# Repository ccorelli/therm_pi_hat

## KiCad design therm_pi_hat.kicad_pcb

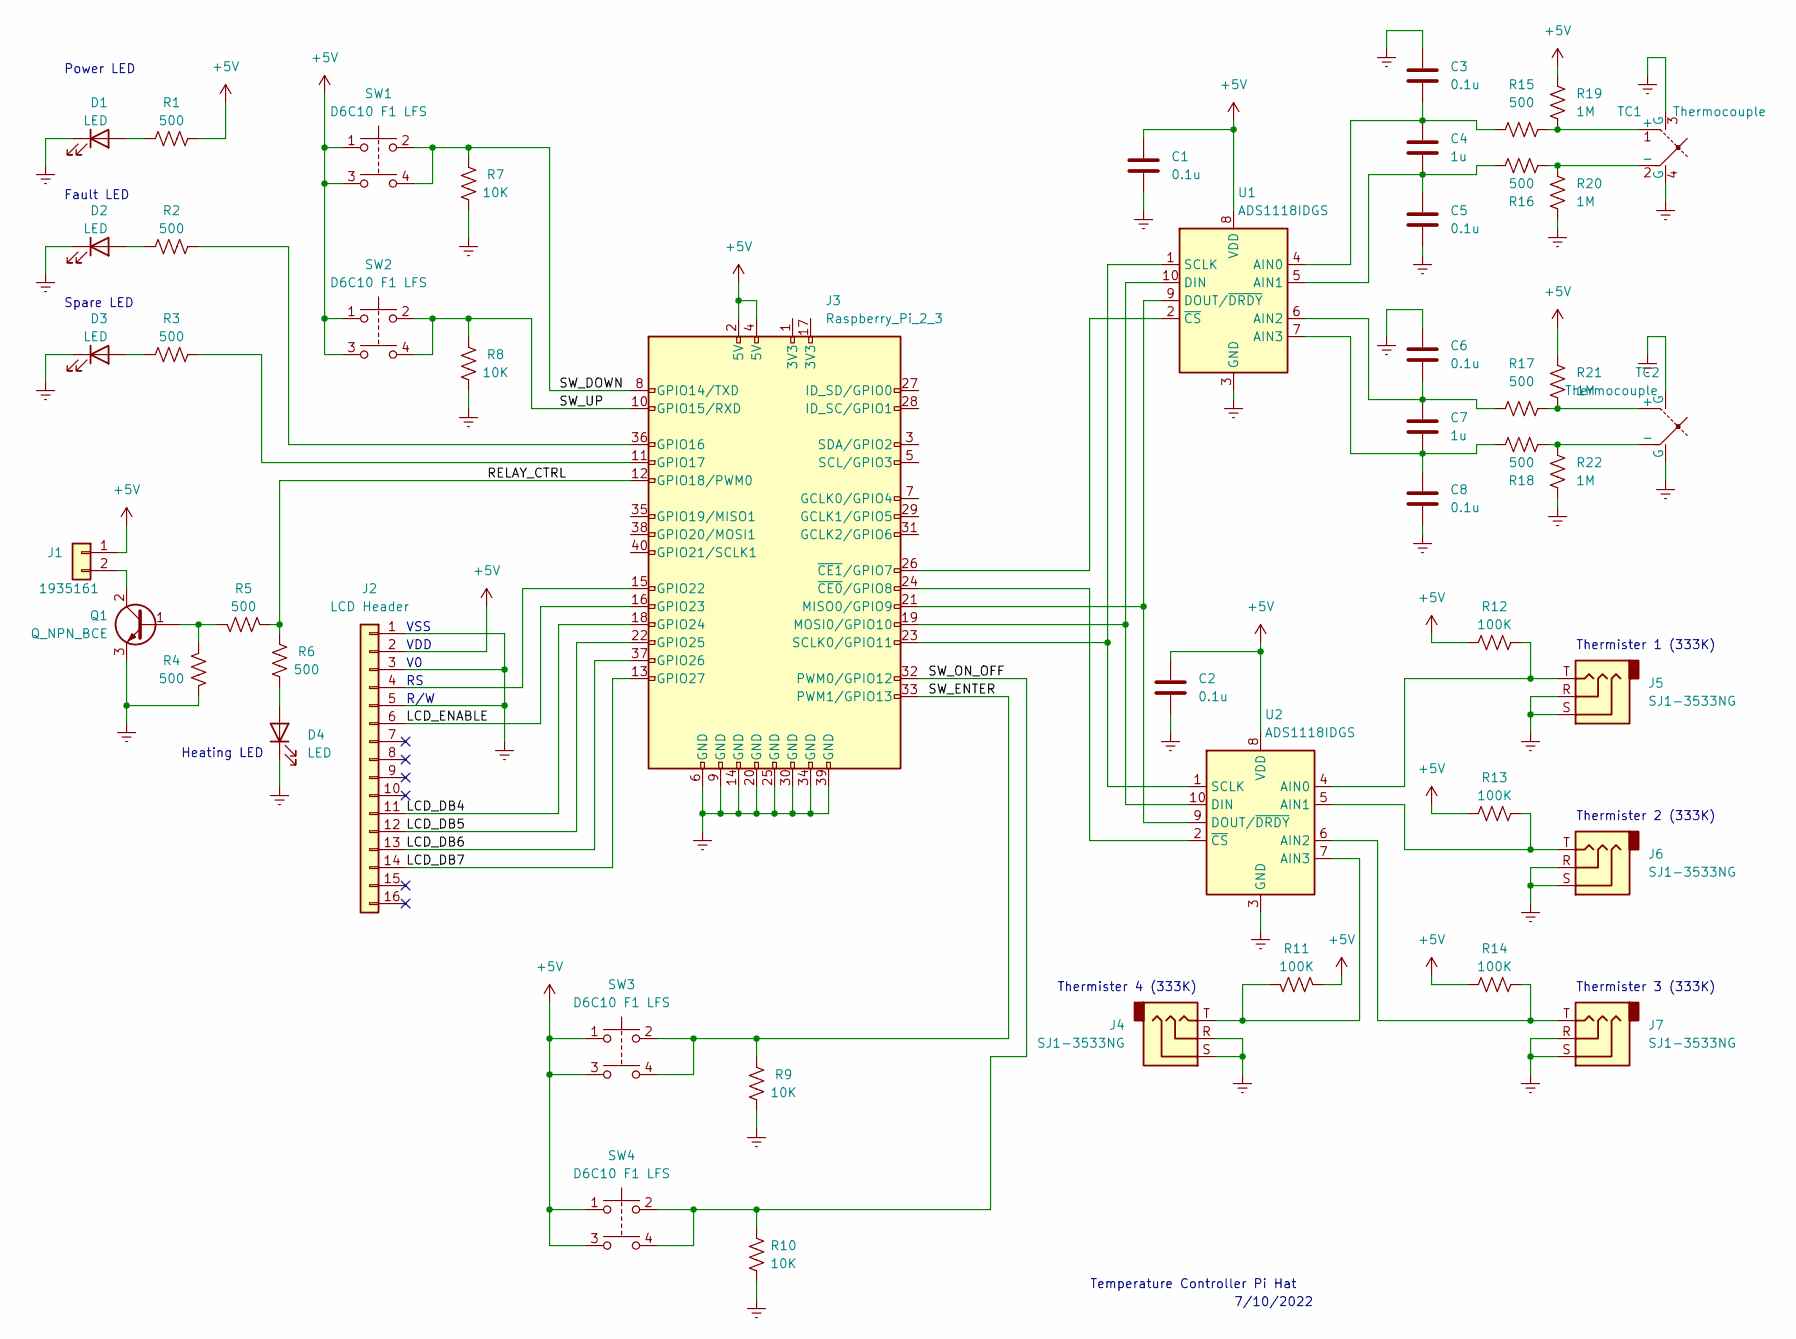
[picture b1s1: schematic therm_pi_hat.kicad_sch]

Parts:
C1, C2, C3, C5, C6, C8: 0.1u; C_Rect_L7.2mm_W3.5mm_P5.00mm_FKS2_FKP2_MKS2_MKP2
C4, C7: 1u; C_Rect_L7.2mm_W3.5mm_P5.00mm_FKS2_FKP2_MKS2_MKP2
D1, D2, D3, D4: LED; LED_D3.0mm_FlatTop
J1: 1935161; PhoenixContact_MSTBVA_2,5_2-G_1x02_P5.00mm_Vertical
J2: LCD Header; PinHeader_1x16_P2.54mm_Vertical
J3: Raspberry_Pi_2_3; PinHeader_2x20_P2.54mm_Vertical
J4, J5, J6, J7: SJ1-3533NG; Jack_3.5mm_CUI_SJ1-3533NG_Horizontal
Q1: Q_NPN_BCE; TO-5-3
R1, R2, R3, R4, R5, R6, R15, R16, R17, R18: 500; R_Axial_DIN0411_L9.9mm_D3.6mm_P12.70mm_Horizontal
R7, R8, R9, R10: 10K; R_Axial_DIN0411_L9.9mm_D3.6mm_P12.70mm_Horizontal
R11, R12, R13, R14: 100K; R_Axial_DIN0411_L9.9mm_D3.6mm_P12.70mm_Horizontal
R19, R20, R21, R22: 1M; R_Axial_DIN0411_L9.9mm_D3.6mm_P12.70mm_Horizontal
SW1, SW2, SW3, SW4: D6C10 F1 LFS; Push_E-Switch_KS01Q01
TC1, TC2: Thermocouple; thermocouple
U1, U2: ADS1118IDGS; TSSOP-10_3x3mm_P0.5mm

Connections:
+5V: C1.1, C2.1, J1.1, J2.2, J3.2 (5V), J3.4 (5V), R1.1, R11.1, R12.1, R13.1, R14.1, R19.1, R21.1, SW1.1, SW1.3, SW2.1, SW2.3, SW3.1, SW3.3, SW4.1, SW4.3, U1.8 (VDD), U2.8 (VDD)
/LCD_DB4: J2.11, J3.18 (GPIO24)
/LCD_DB5: J2.12, J3.22 (GPIO25)
/LCD_DB6: J2.13, J3.37 (GPIO26)
/LCD_DB7: J2.14, J3.13 (GPIO27)
/LCD_ENABLE: J2.6, J3.16 (GPIO23)
/RELAY_CTRL: J3.12 (GPIO18/PWM0), R5.1, R6.1
/SW_DOWN: J3.8 (GPIO14/TXD), R7.1, SW1.2, SW1.4
/SW_ENTER: J3.33 (PWM1/GPIO13), R9.1, SW3.2, SW3.4
/SW_ON_OFF: J3.32 (PWM0/GPIO12), R10.1, SW4.2, SW4.4
/SW_UP: J3.10 (GPIO15/RXD), R8.1, SW2.2, SW2.4
GNDREF: C1.2, C2.2, C3.1, C5.2, C6.1, C8.2, D1.1 (K), D2.1 (K), D3.1 (K), D4.1 (K), J2.1, J2.3, J2.5, J3.6 (GND), J3.9 (GND), J3.14 (GND), J3.20 (GND), J3.25 (GND), J3.30 (GND), J3.34 (GND), J3.39 (GND), J4.R, J4.S, J5.R, J5.S, J6.R, J6.S, J7.R, J7.S, Q1.3 (E), R4.2, R7.2, R8.2, R9.2, R10.2, R20.2, R22.2, TC1.3 (G), TC1.4 (G), TC2.3 (G), TC2.4 (G), U1.3 (GND), U2.3 (GND)
unnamed: C3.2, C4.1, R15.1, U1.4 (AIN0)
unnamed: C4.2, C5.1, R16.2, U1.5 (AIN1)
unnamed: C6.2, C7.1, R17.1, U1.6 (AIN2)
unnamed: C7.2, C8.1, R18.2, U1.7 (AIN3)
unnamed: D1.2 (A), R1.2
unnamed: D2.2 (A), R2.2
unnamed: D3.2 (A), R3.2
unnamed: D4.2 (A), R6.2
unnamed: J1.2, Q1.2 (C)
unnamed: J2.4, J3.15 (GPIO22)
unnamed: J3.11 (GPIO17), R3.1
unnamed: J3.19 (MOSI0/GPIO10), U1.10 (DIN), U2.10 (DIN)
unnamed: J3.21 (MISO0/GPIO9), U1.9 (DOUT/~DRDY), U2.9 (DOUT/~DRDY)
unnamed: J3.23 (SCLK0/GPIO11), U1.1 (SCLK), U2.1 (SCLK)
unnamed: J3.24 (~CE0/GPIO8), U2.2 (~CS)
unnamed: J3.26 (~CE1/GPIO7), U1.2 (~CS)
unnamed: J3.36 (GPIO16), R2.1
unnamed: J4.T, R11.2, U2.7 (AIN3)
unnamed: J5.T, R12.2, U2.4 (AIN0)
unnamed: J6.T, R13.2, U2.5 (AIN1)
unnamed: J7.T, R14.2, U2.6 (AIN2)
unnamed: Q1.1 (B), R4.1, R5.2
unnamed: R15.2, R19.2, TC1.1 (+)
unnamed: R16.1, R20.1, TC1.2 (-)
unnamed: R17.2, R21.2, TC2.1 (+)
unnamed: R18.1, R22.1, TC2.2 (-)

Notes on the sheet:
Heating LED
Thermister 2 (333K)
VSS
VDD
Fault LED
Temperature Controller Pi Hat
Thermister 1 (333K)
Thermister 4 (333K)
Thermister 3 (333K)
Power LED
R/W
7/10/2022
Spare LED

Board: 2 copper layers, 50 parts (0 on the bottom side), 38 nets, no tracks yet.

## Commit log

2023-01-25 added polygon to board cut layer of pcb
2023-01-31 continued placement
2023-02-14 Inital layout complete
